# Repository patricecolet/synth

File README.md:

# synth

Atelier synthé analogique : conception de cartes (KiCad), firmwares Arduino,
interfaces Pure Data et documentation de référence.

Le dépôt regroupe plusieurs projets indépendants. Chacun est autonome —
schémas, firmware et patchs vivent dans le même dossier.

## Projets

| Dossier | Quoi |
|---|---|
| [`PS-101/`](PS-101/) | Le synthé principal : carte mère, VCO, VCF, mixeur d'ondes, firmware et UI Pd |
| [`kobol-expander/`](kobol-expander/) | **Interface MIDI → CV pour RSF Kobol Expander.** Firmware Teensy qui tourne, piloté depuis le séquenceur NiDMI Seq |
| [`sequencer/`](sequencer/) | Séquenceur à base de 74HC595 (KiCad, 2018) |
| [`alimentation/`](alimentation/) | Alimentation symétrique LM723 / LM2596 + masse virtuelle |
| [`xva1/`](xva1/) | Patchs Pd de contrôle pour le moteur XVA1 |
| [`experiments/`](experiments/) | Bancs d'essai : DAC MCP4822 / MCP4921, driver TLC5940, LFO |
| [`reference/`](reference/) | Datasheets et schémas glanés — matière première, **non versionnée** (voir ci-dessous) |

## Détail

### PS-101

Le projet le plus abouti. Un VCO numérique (tables d'ondes en ROM → DAC MCP4822)
piloté par Arduino, avec un chemin analogique classique derrière.

```
PS-101/
├── hardware/          # KiCad : carte mère + sous-cartes
│   ├── PS-101.sch/.kicad_pcb   carte principale
│   ├── vco/           VCO (PS-01_VCO)
│   ├── vcf/           filtre Pro-One (AS3320)
│   ├── vco_mixer/     mixeur d'ondes
│   ├── synth.pretty/  empreintes maison
│   └── trace/         sorties PDF
├── firmware/          # sketches Arduino, du plus ancien au plus récent
│   ├── PS-01/         194 l. — 3× MCP4822, 9 formes d'onde, LFO
│   ├── PS01_TEST/     334 l.
│   ├── PS01_TEST2/    376 l. — 2× MCP4822, 5 ondes, mode DEBUG
│   └── EEPROM/        253 l. — persistance des paramètres
└── pd/                # interface Pure Data
    ├── PS01ui.pd      UI principale
    └── PS01_param.pd  abstraction d'un paramètre (utilisée par PS01ui)
```

Les tables d'ondes (`wave/*.h`) sont volontairement dupliquées dans chaque
sketch : l'IDE Arduino exige qu'un sketch soit autonome.

### kobol-expander

Le projet le plus actif. Un Teensy 2.0 reçoit du MIDI USB et sort du CV vers
le Kobol via un MCP4822 — pitch sur le canal A, cutoff du filtre sur le canal B.

```
kobol-expander/
├── midi-cv/            # le travail actif
│   ├── KobolMidiCV/    firmware Teensy (compile, téléversé)
│   ├── midi-map.json   LA carte MIDI — fait foi pour tout le reste
│   ├── build.sh        compile + téléverse, pose le nom USB « Kobol »
│   ├── tools/          vérificateurs de cohérence, test MIDI sans DAW
│   ├── INTEGRATION.md  lien avec le séquenceur NiDMI Seq
│   └── CALIBRATION.md  échelle du pitch, mesurée
├── v1-first-release/   firmware d'origine, référence intouchée
├── v2-simple/          projet KiCad kobol_V2
├── v3/v4/v5            documentation de vision
└── docs/               mesures électriques du connecteur P1
```

**Le pilotage se fait depuis NiDMI Seq**, le séquenceur VST maison (dépôt
voisin, voir plus bas), auquel on a ajouté un profil d'appareil pour qu'il
affiche « VCF Cutoff » au lieu de « CC 74 ». Le détail, la frontière entre les
deux dépôts et les garde-fous contre la dérive sont dans
[`kobol-expander/midi-cv/INTEGRATION.md`](kobol-expander/midi-cv/INTEGRATION.md).

Le brochage du connecteur P1 du Kobol est relevé dans
[`reference/kobol/Plug.txt`](reference/kobol/Plug.txt).

### xva1

`XVA1.pd` et `comUI.pd` sont deux états du même patch (seules diffèrent des
valeurs de sliders sauvegardées). `paramUI.pd` est l'abstraction qu'ils
instancient.

## Documentation tierce

Le dépôt ne contient **que du travail original**. Les datasheets constructeur,
manuels de service et schémas de synthés commerciaux ne sont pas
redistribuables : ils restent sur le disque local mais sont exclus du suivi
git. Concrètement, un clone trouvera vides :

- `reference/datasheets/`, `reference/kobol/`, `reference/analog-synth/`
- les schémas et PDF de `alimentation/`

Chaque README de dossier liste ce qu'il faut retélécharger et auprès de qui —
voir [`reference/README.md`](reference/README.md) et
[`alimentation/README.md`](alimentation/README.md). Mes propres relevés
(`Plug.txt`, `missing.txt`, `CONSOMATION.txt`, `goldpoint_capa.txt`) sont bien
versionnés, eux.

**L'historique a été purgé** avant la publication : `git filter-repo` a retiré
ces 104 fichiers de **tous** les commits, pas seulement de la dernière version.
Le dépôt est passé de 31 Mo à 2,3 Mo. Un commit qui ne faisait que restaurer un
de ces PDF est devenu vide et a disparu.

Mes propres relevés ont été explicitement conservés à travers la réécriture :
`Plug.txt`, `missing.txt`, `CONSOMATION.txt`, `goldpoint_capa.txt`. Les PDF
sortis de mon propre KiCad (`PS-101/hardware/trace/`, `*_schema.pdf`) aussi.

Les fichiers écartés restent **sur le disque local**, seulement plus dans git.

## Dépôts voisins

Ce dépôt ne contient pas tout l'écosystème. Deux voisins comptent :

Les trois dépôts sont voisins :

```
~/repo/
├── synth/                  ← celui-ci
├── nidmi-seq-vst/          NiDMI Seq — séquenceur VST3/AU/Standalone, porte le profil Kobol
└── nidmi-sequencer-core/   moteur de séquencement, sans lien avec le Kobol
```

`nidmi-seq-vst` exige que `nidmi-sequencer-core` soit son voisin direct : son
CMake y va par un `add_subdirectory` relatif.

Le seul fichier qui traverse la frontière est `midi-map.json`, d'où est
**généré** le profil du plugin. Voir
[`kobol-expander/midi-cv/INTEGRATION.md`](kobol-expander/midi-cv/INTEGRATION.md).

## Conventions

- **Pas de chemin absolu** dans les patchs Pd (`declare -path` en nom nu).
- Les sauvegardes KiCad (`*.bak`, `*-bak`, `*-backups/`) et les caches
  (`fp-info-cache`, `*-cache.lib`) sont **suivis volontairement** : ils
  permettent de rouvrir un projet ancien avec les bonnes empreintes.
  Voir les notes en bas de [`.gitignore`](.gitignore).
- Les BOM exportés depuis KiCad portent le suffixe `.bom.csv`.

## Historique

Le commit initial (`Snapshot initial`) capture le dossier **avant** toute
réorganisation. Tout fichier écarté depuis reste récupérable :

```sh
git show <commit>:<ancien/chemin>          # afficher
git checkout <commit> -- <ancien/chemin>   # restaurer
```

## Licence

Le contenu de ce dépôt — firmwares, schémas KiCad, scripts, documentation —
est publié sous licence [MIT](LICENSE).

Cela ne couvre **que** ce qui est versionné ici. La documentation tierce
(datasheets constructeur, manuels de service, schémas de synthés commerciaux)
n'est pas redistribuable et reste volontairement hors du dépôt : elle est
exclue par [`.gitignore`](.gitignore), et les sources sont listées dans les
README des dossiers concernés.

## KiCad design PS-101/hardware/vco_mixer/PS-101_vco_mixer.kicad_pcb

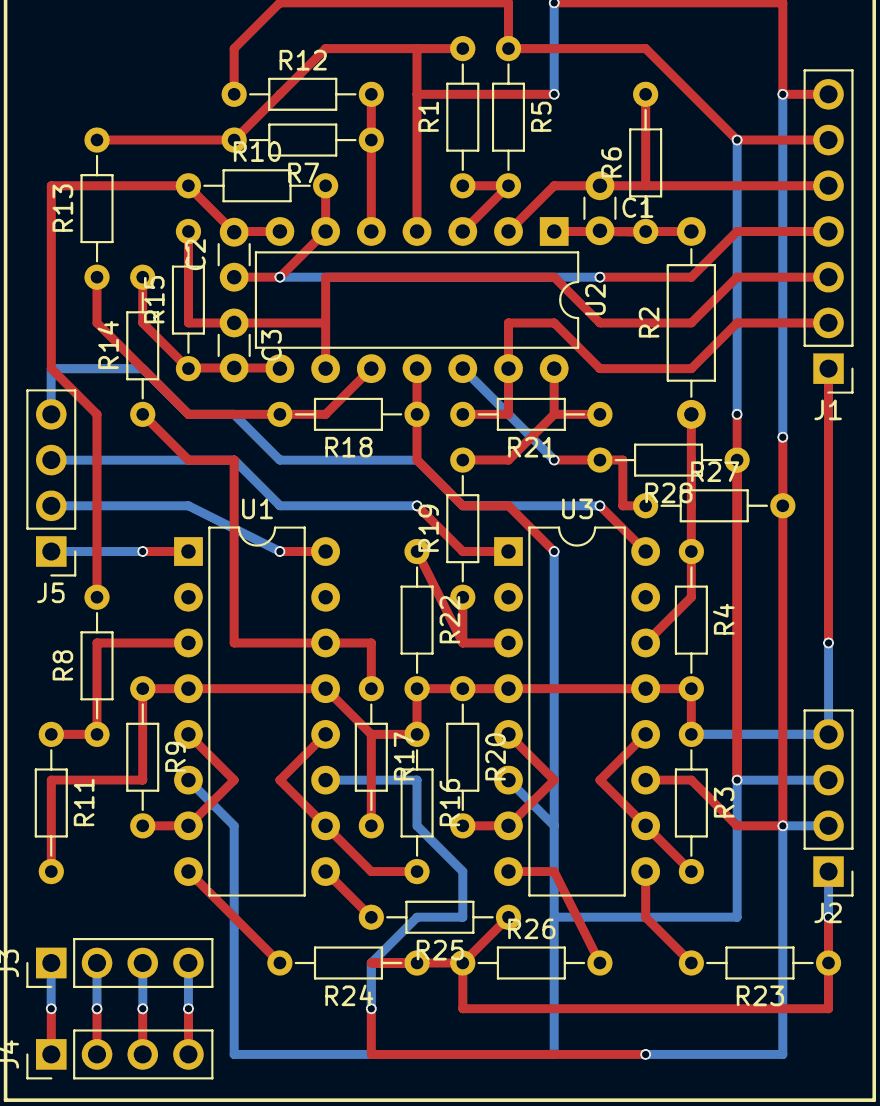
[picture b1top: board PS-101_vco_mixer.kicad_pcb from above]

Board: 2 copper layers, 39 parts (0 on the bottom side), 36 nets.

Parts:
C1, C2, C3: 100p; C_Disc_D3.0mm_W1.6mm_P2.50mm
J1: Conn_01x07_Female; Socket_Strip_Straight_1x07_Pitch2.54mm
J2, J3, J5: Conn_01x04_Male; Pin_Header_Straight_1x04_Pitch2.54mm
J4: Conn_01x04_Female; Socket_Strip_Straight_1x04_Pitch2.54mm
R1, R7, R13, R24, R25: 10K; R_Axial_DIN0204_L3.6mm_D1.6mm_P7.62mm_Horizontal
R2: 33K; R_Axial_DIN0207_L6.3mm_D2.5mm_P10.16mm_Horizontal
R3: 33K; R_Axial_DIN0204_L3.6mm_D1.6mm_P7.62mm_Horizontal
R4, R11, R17, R22: 68; R_Axial_DIN0204_L3.6mm_D1.6mm_P7.62mm_Horizontal
R5, R8, R12, R14, R18, R19: 22K; R_Axial_DIN0204_L3.6mm_D1.6mm_P7.62mm_Horizontal
R6, R10, R15, R21: 100K; R_Axial_DIN0204_L3.6mm_D1.6mm_P7.62mm_Horizontal
R9, R16, R20: 28K; R_Axial_DIN0204_L3.6mm_D1.6mm_P7.62mm_Horizontal
R23: 6.8K; R_Axial_DIN0204_L3.6mm_D1.6mm_P7.62mm_Horizontal
R26: 4.7K; R_Axial_DIN0204_L3.6mm_D1.6mm_P7.62mm_Horizontal
R27: 15K; R_Axial_DIN0204_L3.6mm_D1.6mm_P7.62mm_Horizontal
R28: 47K; R_Axial_DIN0204_L3.6mm_D1.6mm_P7.62mm_Horizontal
U1, U3: LM13700; DIP-16_W7.62mm
U2: TL084; DIP-14_W7.62mm

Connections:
GNDPWR: J1.1, J2.4, R3.1, R4.2, R9.1, R11.2, R16.1, R17.2, R20.1, R22.2, U1.4, U1.13, U3.4, U3.13
unnamed: C1.1, J1.5, R6.2, U2.2
unnamed: C1.2, R2.2, R6.1, U2.1
unnamed: C2.1, J1.4, R10.2, U2.6
unnamed: C2.2, R8.2, R10.1, U2.7
unnamed: C3.1, J1.3, R15.2, U2.9
unnamed: C3.2, R14.2, R15.1, U2.8
unnamed: J1.2, R21.2, U2.13
unnamed: J2.1, R23.1, R24.1, R25.1, R26.1
unnamed: J3.1, J4.1
unnamed: J3.2, J4.2
unnamed: J3.3, J4.3
unnamed: J3.4, J4.4
unnamed: J5.1, U1.1
unnamed: J5.2, U1.16
unnamed: J5.3, U3.1
unnamed: J5.4, U3.16
unnamed: R1.1, R5.2, U2.3
unnamed: R2.1, R4.1, U3.14
unnamed: R3.2, U3.10, U3.12
unnamed: R9.2, U1.5, U1.7
unnamed: R8.1, R11.1, U1.3
unnamed: R7.1, R12.2, U2.5
unnamed: R13.1, R18.2, U2.10
unnamed: R14.1, R17.1, U1.14
unnamed: R16.2, U1.10, U1.12
unnamed: R19.1, R22.1, U3.3
unnamed: R19.2, R21.1, U2.14
unnamed: R20.2, U3.5, U3.7
unnamed: R23.2, U3.9
unnamed: R24.2, U1.8
unnamed: R25.2, U1.9
unnamed: R26.2, U3.8
unnamed: R27.1, R28.2, U2.12
VDD: J1.7, J2.2, R1.2, R7.2, R13.2, R27.2, U1.11, U2.4, U3.11
VEE: J1.6, J2.3, R5.1, R12.1, R18.1, R28.1, U1.6, U2.11, U3.6

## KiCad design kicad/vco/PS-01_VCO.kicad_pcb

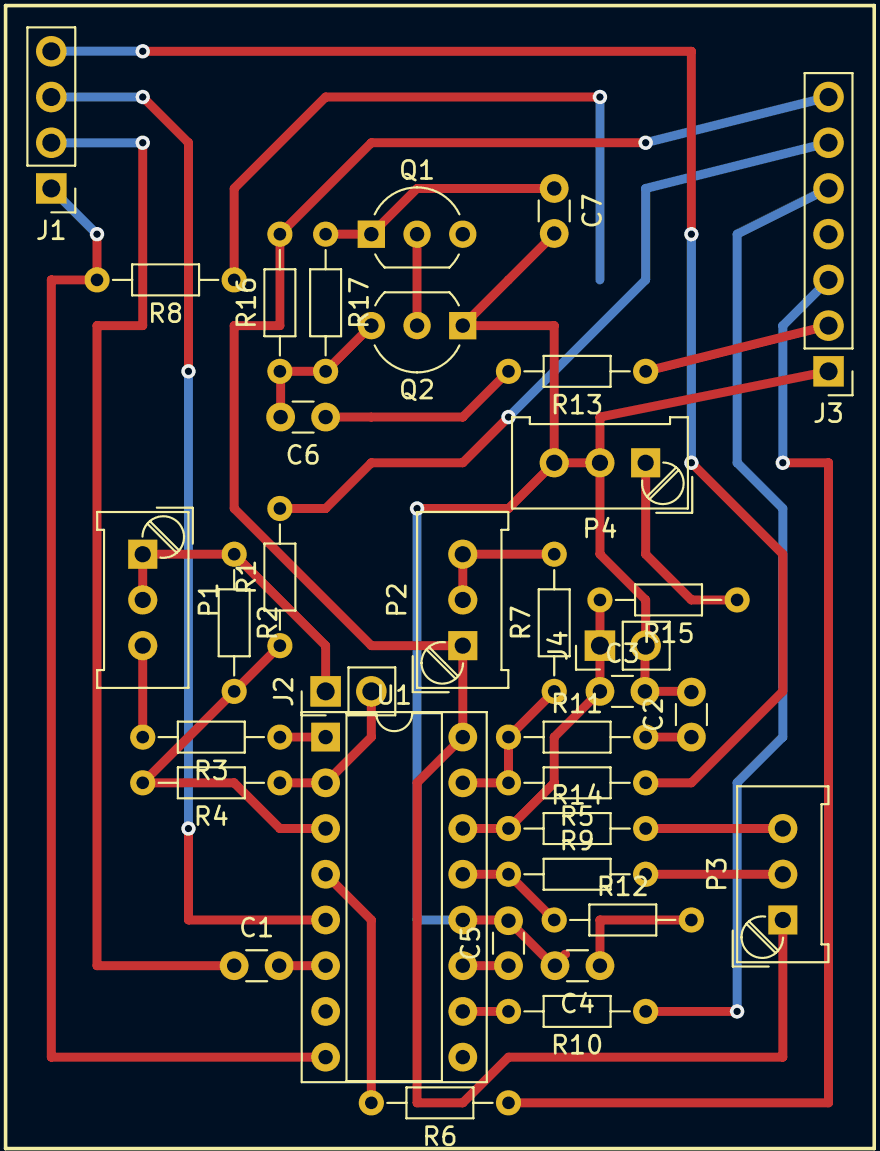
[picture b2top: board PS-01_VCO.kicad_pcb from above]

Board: 2 copper layers, 35 parts (0 on the bottom side), 33 nets.

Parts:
C1, C5: 1nF; C_Disc_D3.0mm_W1.6mm_P2.50mm
C2, C4, C6: 10nF; C_Disc_D3.0mm_W1.6mm_P2.50mm
C3: 560p; C_Disc_D3.0mm_W1.6mm_P2.50mm
C7: 100nF; C_Disc_D3.0mm_W1.6mm_P2.50mm
J1: Conn_01x04_Male; Pin_Header_Straight_1x04_Pitch2.54mm
J2, J4: Conn_01x02_Male; Pin_Header_Straight_1x02_Pitch2.54mm
J3: Conn_01x07_Male; Pin_Header_Straight_1x07_Pitch2.54mm
P1: 5K; Potentiometer_Trimmer_Bourns_PV36W
P2: 100K; Potentiometer_Trimmer_Bourns_PV36W
P3: 10K; Potentiometer_Trimmer_Bourns_PV36W
P4: 500ohm; Potentiometer_Trimmer_Bourns_PV36W
Q1, Q2: 2N3904; TO-92_Inline_Wide
R1: 1K; R_Axial_DIN0204_L3.6mm_D1.6mm_P7.62mm_Horizontal
R2, R4: 5K6; R_Axial_DIN0204_L3.6mm_D1.6mm_P7.62mm_Horizontal
R3: 18K; R_Axial_DIN0204_L3.6mm_D1.6mm_P7.62mm_Horizontal
R5, R13: 100K; R_Axial_DIN0204_L3.6mm_D1.6mm_P7.62mm_Horizontal
R6, R8: 180K; R_Axial_DIN0204_L3.6mm_D1.6mm_P7.62mm_Horizontal
R7: 220K; R_Axial_DIN0204_L3.6mm_D1.6mm_P7.62mm_Horizontal
R9: 1M8; R_Axial_DIN0204_L3.6mm_D1.6mm_P7.62mm_Horizontal
R10: 68K; R_Axial_DIN0204_L3.6mm_D1.6mm_P7.62mm_Horizontal
R11: 470Ohm; R_Axial_DIN0204_L3.6mm_D1.6mm_P7.62mm_Horizontal
R12: 470ohm; R_Axial_DIN0204_L3.6mm_D1.6mm_P7.62mm_Horizontal
R14: 22K; R_Axial_DIN0204_L3.6mm_D1.6mm_P7.62mm_Horizontal
R15: 1K62; R_Axial_DIN0204_L3.6mm_D1.6mm_P7.62mm_Horizontal
R16: 4.7K; R_Axial_DIN0204_L3.6mm_D1.6mm_P7.62mm_Horizontal
R17: 47K; R_Axial_DIN0204_L3.6mm_D1.6mm_P7.62mm_Horizontal
U1: AS3340; DIP-16_W7.62mm_Socket

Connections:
GND: C2.2, C3.2, C4.2, C5.2, C7.2, J3.1, J4.2, P4.2, P4.3, Q2.1, U1.12
unnamed: C1.1, J1.2
unnamed: C1.2, U1.6
unnamed: C2.1, R11.2
unnamed: C3.1, J4.1, R14.1, R15.2, U1.14
unnamed: C4.1, R12.2
unnamed: C5.1, U1.11
unnamed: C6.1, R13.2
unnamed: C6.2, Q2.3, R16.1, R17.2
unnamed: C7.1, Q1.1, R17.1
unnamed: J1.1, R8.2, U1.8
unnamed: J1.3, U1.5
unnamed: J1.4, R5.1
unnamed: J2.1, P1.1, P1.2, R2.1
unnamed: J2.2, R4.1, U1.2
unnamed: J3.2, R13.1
unnamed: J3.3, R6.1
unnamed: J3.4, R8.1
unnamed: J3.5, R10.1
unnamed: P1.3, R3.2
unnamed: P2.2, P2.3, R7.2
unnamed: P3.2, R9.2
unnamed: P3.3, R14.2
unnamed: P4.1, R15.1
unnamed: Q1.2, Q2.2
unnamed: R1.1, R2.2, R4.2, U1.3
unnamed: R3.1, U1.1
unnamed: R6.2, U1.4
unnamed: R10.2, U1.10
unnamed: R5.2, R7.1, R11.1, U1.15
unnamed: R9.1, R12.1, U1.13
VCC: J3.7, P2.1, P3.1, R16.2, U1.16
VSS: J3.6, R1.2

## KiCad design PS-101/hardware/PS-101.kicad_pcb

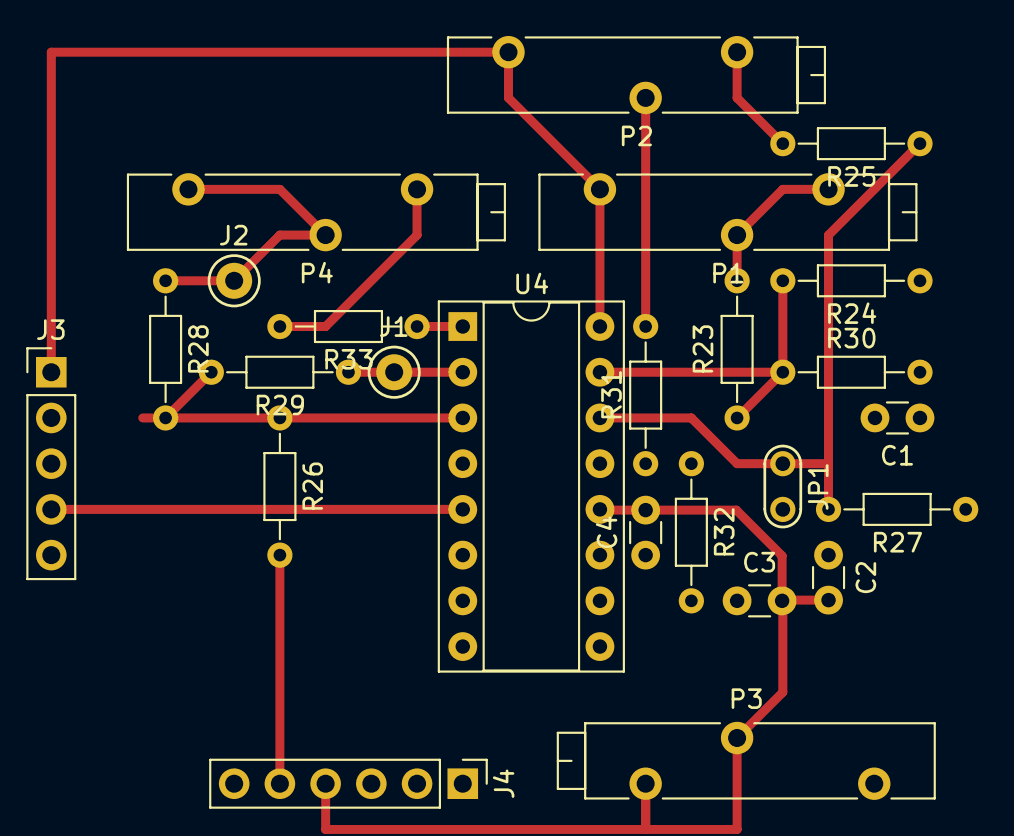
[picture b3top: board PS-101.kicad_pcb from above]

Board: 2 copper layers, 25 parts (0 on the bottom side), 23 nets.

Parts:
C1, C3: 10nF; C_Disc_D3.0mm_W1.6mm_P2.50mm
C2: 560p; C_Disc_D3.0mm_W1.6mm_P2.50mm
C4: 1nF; C_Disc_D3.0mm_W1.6mm_P2.50mm
J1: T1; Test_Point_Keystone_5000-5004_Miniature
J2: T2; Test_Point_Keystone_5000-5004_Miniature
J3: Conn_01x05_Male; Pin_Header_Straight_1x05_Pitch2.54mm
J4: Conn_01x06_Male; Pin_Header_Straight_1x06_Pitch2.54mm
JP1: tune; Test_Point
P1: 100K; Potentiometer_Trimmer_Bourns_3005
P2: 10K; Potentiometer_Trimmer_Bourns_3005
P3: 500ohm; Potentiometer_Trimmer_Bourns_3005
P4: 5K; Potentiometer_Trimmer_Bourns_3005
R23: 220K; R_Axial_DIN0204_L3.6mm_D1.6mm_P7.62mm_Horizontal
R24: 100K; R_Axial_DIN0204_L3.6mm_D1.6mm_P7.62mm_Horizontal
R25: 22K; R_Axial_DIN0204_L3.6mm_D1.6mm_P7.62mm_Horizontal
R26: 1K; R_Axial_DIN0204_L3.6mm_D1.6mm_P7.62mm_Horizontal
R27: 1K62; R_Axial_DIN0204_L3.6mm_D1.6mm_P7.62mm_Horizontal
R28, R29: 5K6; R_Axial_DIN0204_L3.6mm_D1.6mm_P7.62mm_Horizontal
R30: 470Ohm; R_Axial_DIN0204_L3.6mm_D1.6mm_P7.62mm_Horizontal
R31: 1M8; R_Axial_DIN0204_L3.6mm_D1.6mm_P7.62mm_Horizontal
R32: 470ohm; R_Axial_DIN0204_L3.6mm_D1.6mm_P7.62mm_Horizontal
R33: 18K; R_Axial_DIN0204_L3.6mm_D1.6mm_P7.62mm_Horizontal
U4: AS3340; DIP-16_W7.62mm_Socket

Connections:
/vco/cv_in: J3.5, R24.1
/vco/pulsewidth: J3.4, U4.5
/vco/pwm_out: J4.3, U4.4
/vco/sawtooth_out: J4.2, U4.8
/vco/triangle_out: J4.1, U4.10
GND: C1.2, C2.2, C3.2, C4.2, J3.3, J4.4, P3.2, P3.3, U4.12
unnamed: C1.1, R30.2
unnamed: C2.1, JP1.1, R25.1, R27.2, U4.14
unnamed: C3.1, R32.2
unnamed: C4.1, U4.11
unnamed: J1.1, R29.1, U4.2
unnamed: J2.1, P4.1, P4.2, R28.1
unnamed: P1.2, P1.3, R23.2
unnamed: P2.2, R31.2
unnamed: P2.3, R25.2
unnamed: P3.1, R27.1
unnamed: P4.3, R33.2
unnamed: R23.1, R24.2, R30.1, U4.15
unnamed: R26.1, R28.2, R29.2, U4.3
unnamed: R31.1, R32.1, U4.13
unnamed: R33.1, U4.1
VCC: J3.1, J4.6, P1.1, P2.1, U4.16
VSS: J3.2, J4.5, R26.2

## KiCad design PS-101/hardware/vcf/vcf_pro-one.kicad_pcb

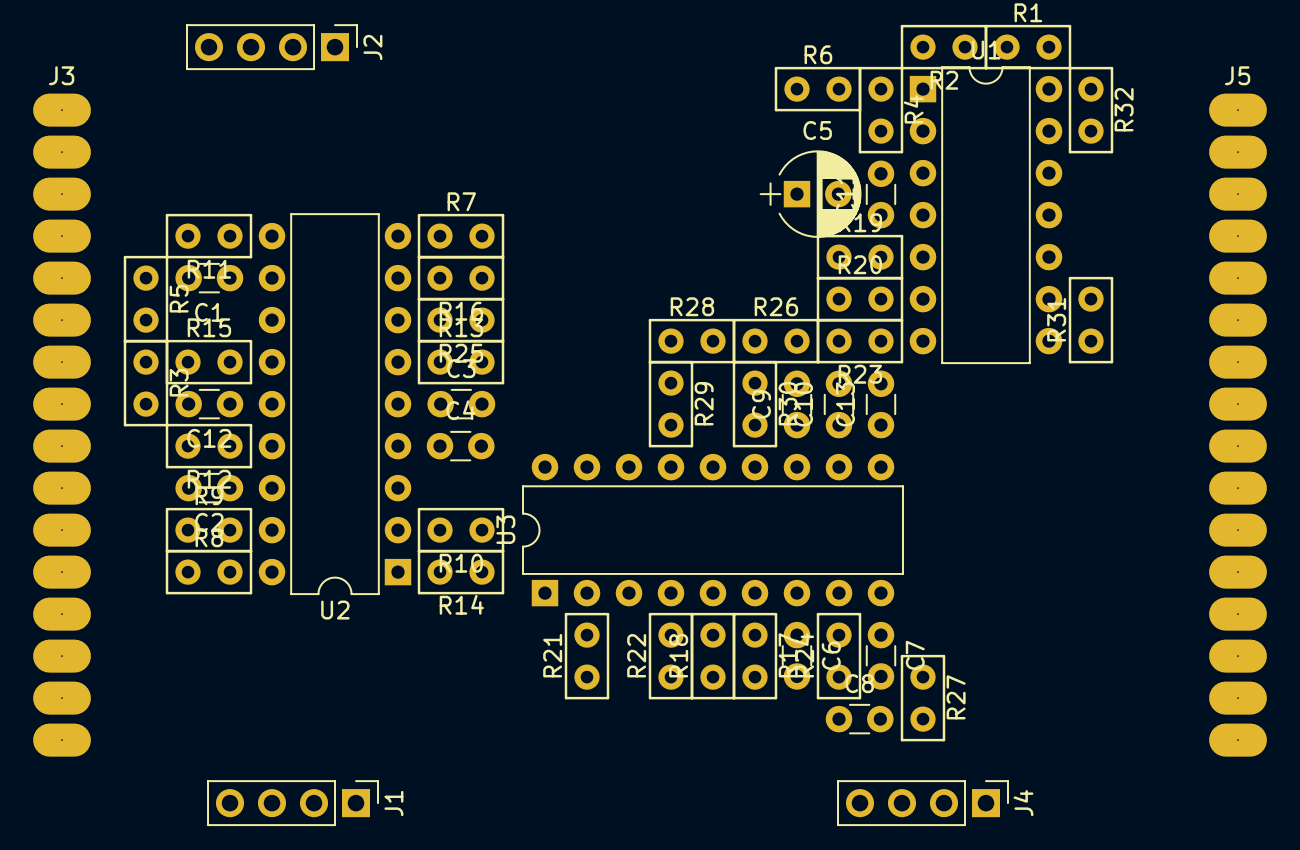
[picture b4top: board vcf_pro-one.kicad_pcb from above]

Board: 2 copper layers, 53 parts (0 on the bottom side), 53 nets, no tracks yet.

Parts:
C1, C2, C3, C4: 150p; C_Disc_D3.0mm_W1.6mm_P2.50mm
C5: 2u2; CP_Radial_D5.0mm_P2.50mm
C6, C9: 1n; C_Disc_D3.0mm_W1.6mm_P2.50mm
C7, C10: 5n; C_Disc_D3.0mm_W1.6mm_P2.50mm
C8, C11, C12, C13: 100n; C_Disc_D3.0mm_W1.6mm_P2.50mm
J1, J2, J4: Conn_01x04_Female; Socket_Strip_Straight_1x04_Pitch2.54mm
J3, J5: Conn_01x16_Male; card_16_slot
R1, R4: 47k; radial
R2, R3, R11, R12, R13, R14, R20, R22, R30: 100k; radial
R5: 1k8; radial
R6: 120k; radial
R7: 200k; radial
R8, R9, R10: 91k; radial
R15: 1k5; radial
R16: 3k; radial
R17, R26: 33k; radial
R18, R28: 1k; radial
R19: 68k; radial
R21, R29: 150k; radial
R23: 240k; radial
R24: 6.8k; radial
R25, R31, R32: 51k; radial
R27: 680; radial
U1: TL084; DIP-14_W7.62mm
U2: AS3320; DIP-18_W7.62mm
U3: AS3330; DIP-18_W7.62mm

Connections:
CV_PWM: J3.11, J4.3
CV_audio: J3.16, R26.2
CV_cutoff: J3.14, R3.2
CV_freq: J3.12, J4.4
CV_noise: J1.3, J3.8
CV_pulsew: J1.2, J3.7
CV_res: J3.13, R7.2
CV_saw: J1.1, J3.6
CV_tri: J1.4, J3.9
CV_vca: J3.15, R17.2
GND: C1.2, C2.2, C3.2, C4.2, C10.2, C11.2, C12.2, C13.2, J2.4, J3.1, J5.16, R5.1, R16.1, R18.1, R19.1, R20.1, R28.1, U1.2, U1.10, U1.13, U2.3, U3.17, U3.18
unnamed: C1.1, U2.11
unnamed: C2.1, U2.16
unnamed: C3.1, U2.5
unnamed: C4.1, U2.4
unnamed: C5.1, R11.1, U2.10
unnamed: C5.2, R19.2, U1.5
unnamed: C6.1, U3.7
unnamed: C6.2, R21.2, U3.2
unnamed: C7.1, U3.9
unnamed: C8.1, R24.1, R27.2, U3.5
unnamed: C8.2, R24.2, U3.8
unnamed: C9.1, U3.12
unnamed: C9.2, R29.2, U3.15
unnamed: C10.1, U3.11
unnamed: R1.1, R2.1, R4.2, U1.3
unnamed: R3.1, R5.2, U2.12
unnamed: R4.1, R6.2, U1.1
unnamed: R7.1, U2.9
unnamed: R10.1, R14.1, U2.7
unnamed: R10.2, R13.2, U2.2
unnamed: R8.2, R11.2, U2.18
unnamed: R8.1, R12.1, U2.15
unnamed: R9.2, R12.2, U2.17
unnamed: R9.1, R13.1, U2.6
unnamed: R6.1, R14.2, U2.1
unnamed: R15.2, U2.13
unnamed: R16.2, R25.2, U2.8
unnamed: R17.1, R18.2, U3.6
unnamed: R20.2, R23.2, U1.6
unnamed: R22.2, U3.4
unnamed: R26.1, R28.2, U3.14
unnamed: R30.2, U3.13
unnamed: R31.2, U1.9, U3.1
unnamed: R32.2, U1.12, U3.16
Sync_in: J3.10, J4.1, J4.2, J5.14
VCC: C11.1, C12.1, C13.1, J2.2, J3.3, R21.1, R29.1, U1.4, U2.14, U3.10
VDD: C7.2, J2.3, J3.2, R15.1, R27.1, U1.11, U3.3
audio_in: J5.15, R30.1
audio_out: R1.2, R32.1, U1.14
vca_out: J3.5, R31.1, U1.8
vcf_in: J2.1, J3.4, R2.2
vcf_out: R22.1, R23.1, R25.1, U1.7
